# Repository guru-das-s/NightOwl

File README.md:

# NightOwl
A real­time, wearable, nighttime seizure notification and reporting system.

Effective treatment of epilepsy requires accurate reporting of occurrences of seizures and duration of seizures. Oftentimes the data available is inaccurate because of natural inefficiencies in caregivers. NightOwl addresses this problem by creating an always-on system that detects and monitors seizure activity.

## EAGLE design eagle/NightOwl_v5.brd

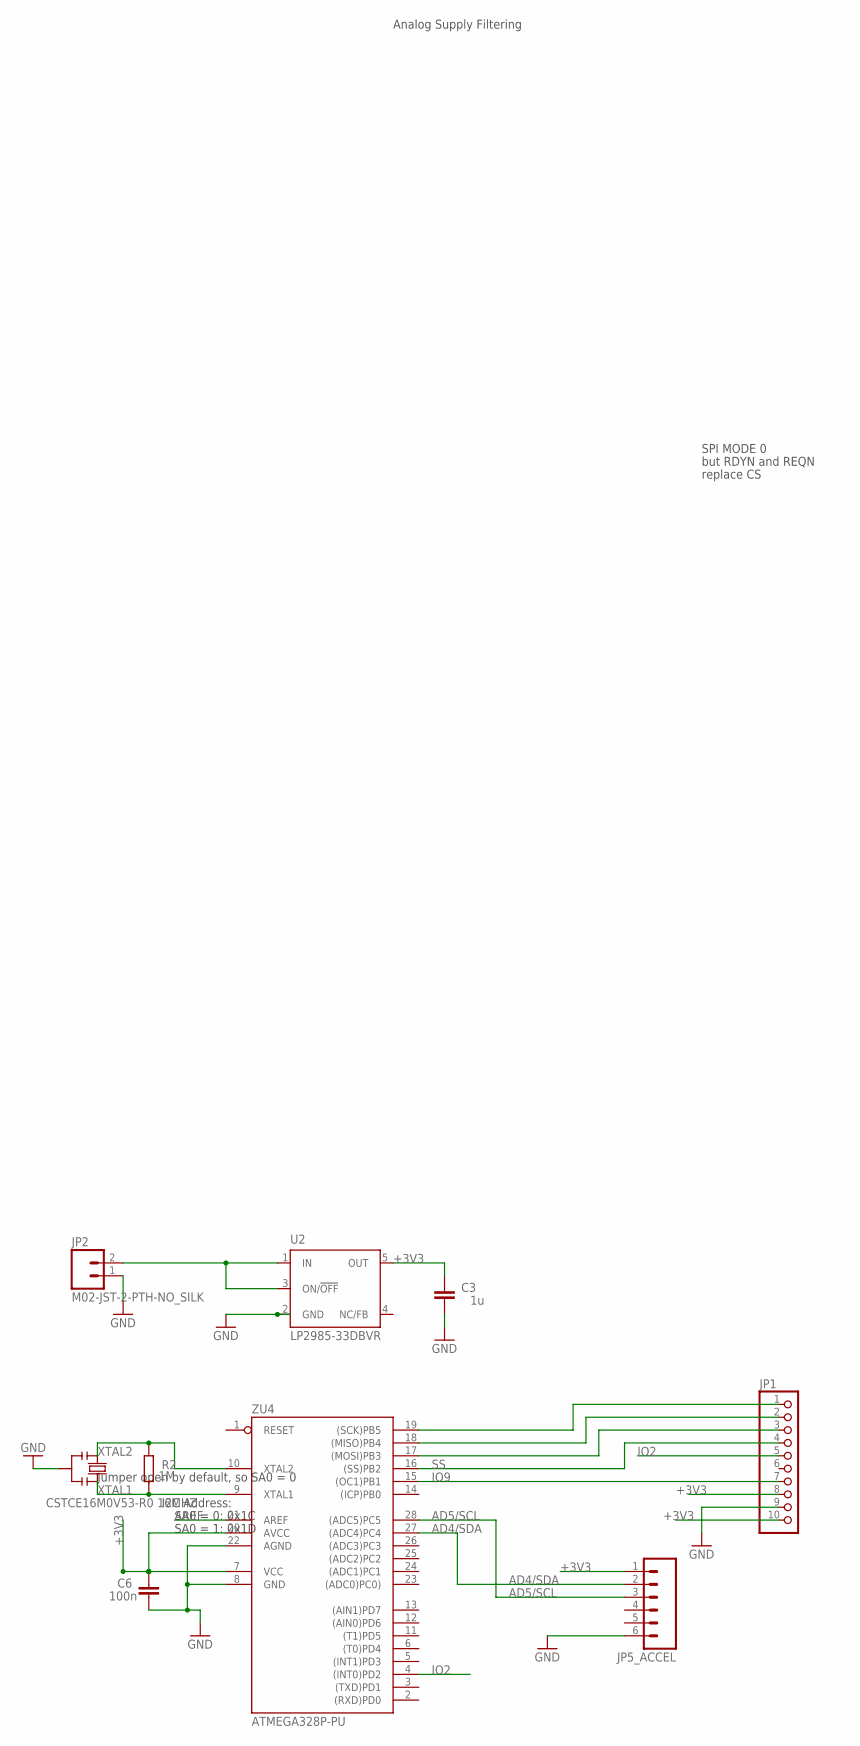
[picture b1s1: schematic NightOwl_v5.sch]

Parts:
C3: 1u; C0603-ROUND
C6: 100n; C0603-ROUND
JP1: HEADER-1X1070MIL; 1X10_ROUND70
JP2: M02-JST-2-PTH-NO_SILK; JST-2-PTH-NS
JP5_ACCEL: M06SIP; 1X06
R2: 1M; R0603-ROUND
U2: LP2985-33DBVR; SOT23-DBV
Y2: CSTCE16M0V53-R0 16MHZ; RESONATOR
ZU4: ATMEGA328P-PU; DIL28-3

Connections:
+3V3: C3.2, C6.2, JP1.8, JP1.10, JP5_ACCEL.1, U2.5 (OUT), ZU4.7 (VCC), ZU4.20 (AVCC)
AD4/SDA: JP5_ACCEL.2, ZU4.27 ((ADC4)PC4)
AD5/SCL: JP5_ACCEL.3, ZU4.28 ((ADC5)PC5)
AREF: ZU4.21 (AREF)
GND: C3.1, C6.1, JP1.9, JP2.1, JP5_ACCEL.6, U2.2 (GND), Y2.2, ZU4.8 (GND), ZU4.22 (AGND)
IO2: JP1.5, ZU4.4 ((INT0)PD2)
IO9: JP1.7, ZU4.15 ((OC1)PB1)
MISO: JP1.2, ZU4.18 ((MISO)PB4)
MOSI: JP1.3, ZU4.17 ((MOSI)PB3)
unnamed: JP2.2, U2.1 (IN), U2.3 (ON/!OFF)
SCK: JP1.1, ZU4.19 ((SCK)PB5)
SS: JP1.4, ZU4.16 ((SS)PB2)
XTAL1: R2.1, Y2.3, ZU4.9 (XTAL1)
XTAL2: R2.2, Y2.1, ZU4.10 (XTAL2)

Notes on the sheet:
I2C Address:
SA0 = 0: 0x1C
SA0 = 1: 0x1D
Jumper open by default, so SA0 = 0
Analog Supply Filtering
SPI MODE 0
but RDYN and REQN
replace CS

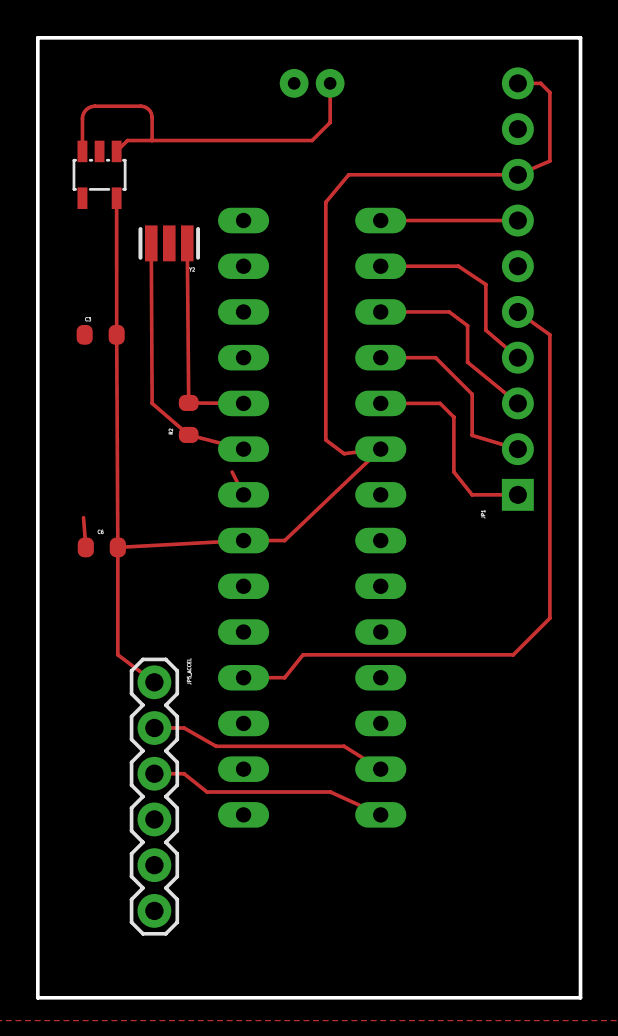
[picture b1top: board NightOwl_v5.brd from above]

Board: 2 copper layers, 30.1 x 53.3 mm, 9 parts (1 on the bottom side), 13 nets.

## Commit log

2015-03-13 Commit to repository
    Final deliverables for the NightOwl project: Arduino code, Eagle
    PCB design files, and project report.

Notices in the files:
parts and their libraries:
microbuilder: This work is placed in the public domain, and may be freely used for commercial and non-commercial work with the following conditions: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
SparkFun-Connectors: Licensing: Creative Commons ShareAlike 4.0 International - https://creativecommons.org/licenses/by-sa/4.0
